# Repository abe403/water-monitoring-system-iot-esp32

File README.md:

# Water Monitoring System

An event-driven IoT telemetry pipeline from ESP32 sensor nodes through
Apache Kafka to a TimescaleDB-backed operator console, with anomaly
detection via time-series baselines and (planned) LSTM inference.

Built on top of [FerranST's open-source ESP32-C3 water-tank hardware and
firmware](https://github.com/FerranST) — see [ATTRIBUTION.md](ATTRIBUTION.md).

## Architecture

Full design, durability chain analysis, and OOD rationale:
[docs/ARCHITECTURE.md](docs/ARCHITECTURE.md)
md)

```
ESP32-C3 ──MQTT QoS1──▶ Mosquitto ──▶ ingest-gateway ──▶ Kafka ──▶ stream-processor
                                         (acks=all)        │              │
                                                           ▼              ▼
                                                    timescale-sink   inference
                                                     (idempotent)       │
                                                           │            ▼
                                                    TimescaleDB    alert-service
                                                           │            │
                                                           ▼            ▼
                                                       operations-api ──▶ console
```

## Repository layout

```
firmware/         ESPHome configs + external components (ESP32-C3 edge nodes)
hardware/         KiCad PCB design (rev-3, solar-powered)
console/          React 19 + TypeScript operator console (REST + STOMP/WebSocket)
platform/         Java 25 / Spring Boot 3.5, Gradle multi-module
  domain/           pure hexagonal core — zero framework imports (ArchUnit-enforced)
  ingest-gateway/   MQTT → Kafka durability chain (acks=all, idempotent producer)
  stream-processor/ Kafka Streams: calibration, quality flags, gap detection
  alert-service/    anomaly score consumer, alert lifecycle with hysteresis
  operations-api/   REST + WebSocket (STOMP) for the operator console
  timescale-sink/   idempotent upsert, Flyway migrations, continuous aggregates
  testing-support/  shared test fixtures
ml/               Python: feature engineering, training pipeline, anomaly detectors
simulator/        synthetic telemetry + fault injection, same 20-byte wire format
infra/            Docker Compose (Kafka KRaft, Mosquitto, TimescaleDB, Prometheus, Grafana)
tools/chaos/       3-broker conservation test with broker fault injection
docs/             architecture, ADRs, claims mapping
```

## Features

- **Firmware**: two ESPHome configs (sensing node + pump controller) validated
  against ESPHome 2026.8.1. The original fatal filter-chain bug (device never
  produced a reading due to EMA starvation under deep sleep) is fixed.
  Pump controller has dry-run protection and runtime cutoff.
- **On-device durability**: `telemetry_outbox` external component — RTC ring
  buffer surviving deep sleep, monotonic sequence numbers, application-level
  end-to-end acknowledgement (stronger than MQTT PUBACK).
- **Java platform**: full 7-module Gradle build passes. Tests cover the
  framework-free domain, MQTT→Kafka durability ordering, Kafka Streams
  enrichment and gap emission, Timescale consumer mapping, alert hysteresis,
  and Kafka→STOMP live telemetry. All adapters are wired.
- **Python ML**: 14 tests passing. Template Method training pipeline, temporal
  split with embargo, z-score/threshold/ensemble baseline detectors, full
  pipeline end-to-end on synthetic data.
- **Simulator**: 8 tests passing. Byte-identical wire encoding to the
  firmware and Java decoder.
- **Durability test**: a kind-based 3-broker Kafka harness publishes through
  MQTT and the real ingest gateway, deletes a broker during sustained load,
  and separately reports missing, unexpected, duplicate, malformed, and
  application-ack results. A recorded Podman-backed run conserved 4,000/4,000
  unique records with complete application acknowledgements while replacing
  a broker at RF=3 and `min.insync.replicas=2`; all partitions returned to
  full ISR with none unavailable or under-replicated. Its pure conservation
  oracle has 3 tests.
- **TimescaleDB schema**: 7 Flyway migrations covering hypertables, device
  registry, calibration profiles, alert table, ingest gap tracking,
  continuous aggregates (1min/1hr), and compression/retention policies.
- **Operator console**: a responsive React 19/TypeScript interface replaces
  Home Assistant for day-to-day monitoring. It provides the fleet overview,
  tank level and telemetry history, data-quality and gap diagnostics, active
  alert acknowledgement/resolution, and live STOMP updates through the same
  origin as the REST API. Seven frontend tests cover data normalization and
  the critical tank and alert surfaces.

Local verification currently covers 46 Java tests, 14 ML tests, 8 simulator
tests, 3 conservation-oracle tests, and 7 console tests: 78 tests total.

## To-Do List

The complete local pipeline has now run under Podman: a 40-record MQTT load
was conserved into Kafka with complete application acknowledgements, persisted
as 40 unique TimescaleDB rows, and exposed through the operations API. The
alert Kafka consumer and acknowledge/resolve API lifecycle were also exercised.
The replicated failure-injection run also completed successfully with 4,000
expected, observed, and unique records and no loss, duplicates, malformed
records, unexpected records, or publish errors. Real-hardware validation and
the field-data/LSTM campaign remain open.

## Prerequisites

- JDK 25 (tested with Amazon Corretto)
- Python 3.11+
- Podman plus `podman-compose` (default), or Docker Compose
- ESPHome CLI (for firmware flashing)

## Quick start

```bash
# Java platform
cd platform && ./gradlew build

# Python ML
cd ml && pip install -e ".[dev]" && pytest

# Simulator
cd simulator && pip install -e ".[dev]" && pytest

# React operator console (development server)
cd console && npm ci && npm run dev

# Full local stack (Podman default)
python -m pip install podman-compose
make up

# Docker-compatible alternative
make up CONTAINER_ENGINE=docker

# Repeat the local 40-record conservation smoke test
make conservation-local

# Three-broker failure-injection test (requires kind and kubectl)
make conservation
```

The Compose deployment serves the operator console at `http://localhost:8080`.
Nginx keeps REST (`/api/`) and STOMP/SockJS (`/ws/`) on that same origin and
proxies them to `operations-api`; no Home Assistant runtime is required.

On Windows, invoke the harness with Git Bash explicitly so `bash` does not
resolve to the Podman-machine WSL distribution:

```powershell
$env:CONTAINER_ENGINE = "podman"
$env:KIND_PROVIDER = "podman"
& "C:\Program Files\Git\bin\bash.exe" tools/chaos/run-kind.sh
```

### Windows Podman port forwarding

If Podman's Windows VirtioProxy is unhealthy, the published container ports
may appear to be listening locally while refusing connections. The portable
helper [tools/podman-port-forward.ps1](tools/podman-port-forward.ps1) uses the
Podman machine's OpenSSH endpoint and dynamically discovered container IPs,
without requiring Administrator/HNS access. It forwards the React console to
`localhost:8080`, operations API to `localhost:8084`, MQTT to
`localhost:1883`, Kafka to `localhost:9092`, and
TimescaleDB to `localhost:15432` (the host's usual PostgreSQL port, 5432, is
left untouched). When broken VirtioProxy listeners occupy those ports, the
zero-argument workflow automatically falls back to `18080` for the console,
`18084` for the API, `11883` for MQTT, and `19092` for Kafka;
`forward-status` reports the actual persisted mappings.

```powershell
# Start, verify, inspect, and stop the tunnel
make forward-start
make forward-test
make forward-status
make forward-stop
```

The helper stores only a PID and endpoint metadata under
`%LOCALAPPDATA%\water-monitoring-system-iot-esp32`; logs are stored beside it.
`Start` is idempotent and refreshes stale container IPs. It refuses to kill
unrelated processes. Pass `-StrictPorts` to demand the exact default ports
after removing a published mapping; otherwise Docker remains supported by the
normal Compose targets and this helper is a Windows Podman fallback.

## Decisions

Architectural decisions are recorded in `docs/DECISIONS/`:

- [0000](docs/DECISIONS/0000-security-remediation.md) — Security remediation
- [0001](docs/DECISIONS/0001-mqtt-over-native-api.md) — MQTT over HA native API
- [0002](docs/DECISIONS/0002-server-side-calibration.md) — Server-side calibration
- [0003](docs/DECISIONS/0003-keep-arduino-framework.md) — Keep Arduino framework
- [0004](docs/DECISIONS/0004-server-side-liveness.md) — Server-side liveness
- [0005](docs/DECISIONS/0005-pod-structs-in-rtc-memory.md) — POD structs in RTC memory
- [0006](docs/DECISIONS/0006-dry-run-protection.md) — Dry-run protection fails closed

## License

See [LICENSE](LICENSE).

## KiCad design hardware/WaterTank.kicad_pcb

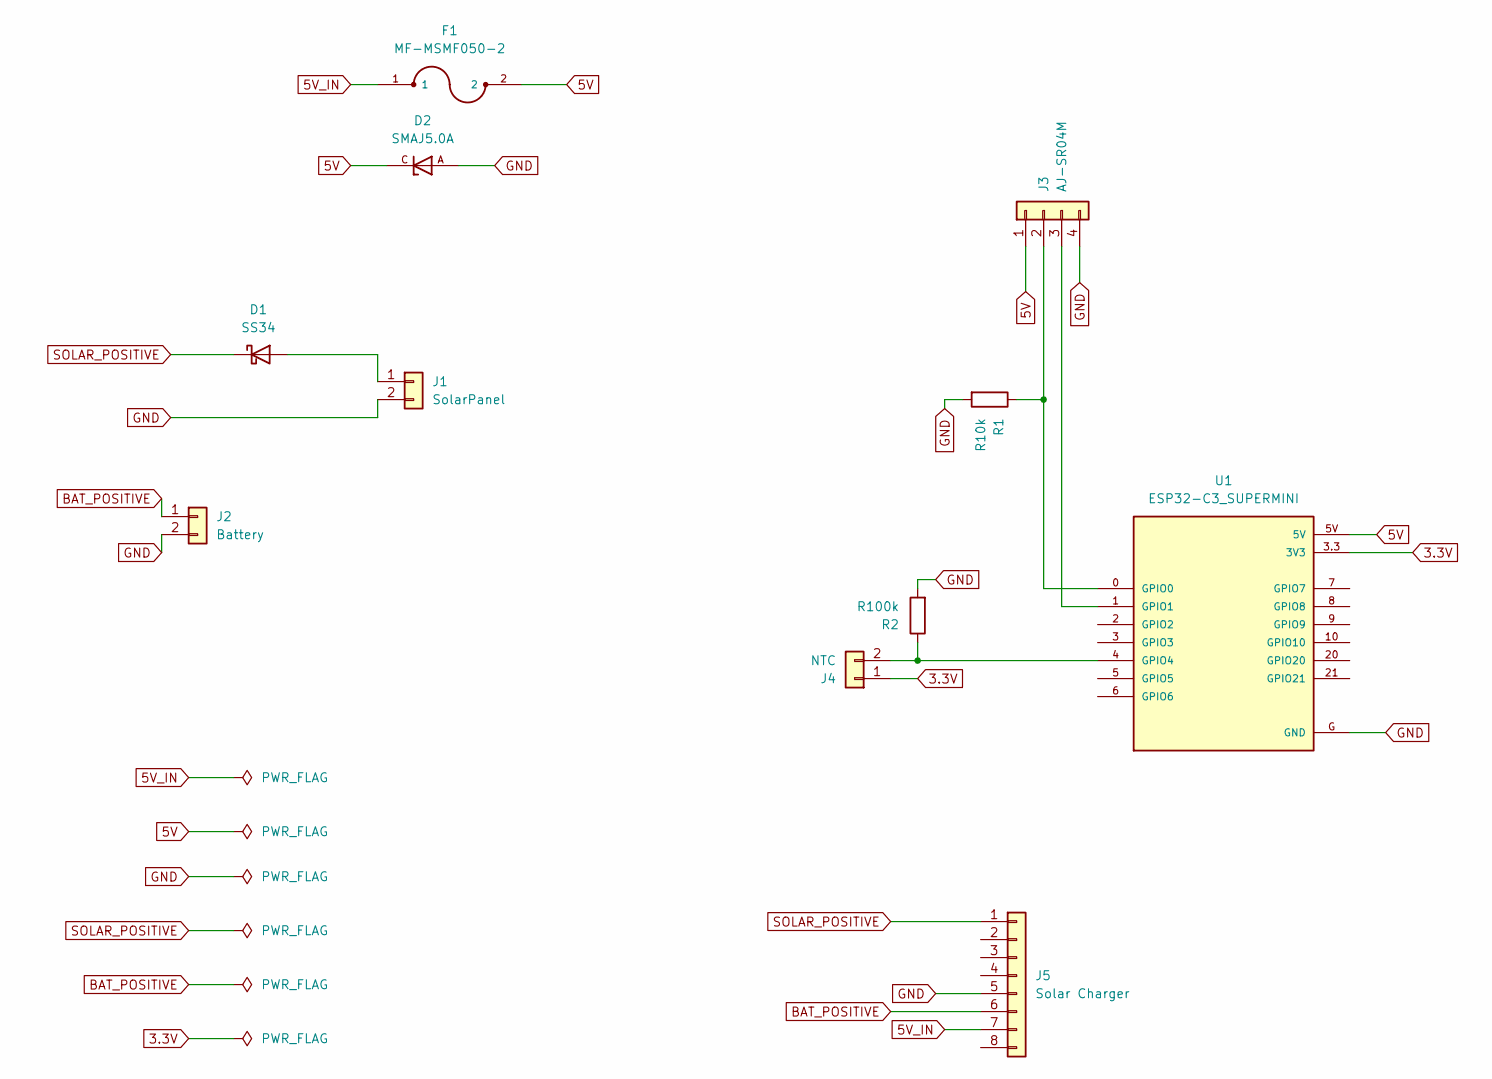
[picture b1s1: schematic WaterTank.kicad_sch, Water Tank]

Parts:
D1: SS34; D_SMA_Handsoldering
D2: SMAJ5.0A; DIOM4325X250N; PARTREV S2102
F1: MF-MSMF050-2; FUSM4632X85; DigiKey_Part_Number MF-MSMF050-2TR-ND
J1: SolarPanel; JST_XH_B2B-XH-A_1x02_P2.50mm_Vertical
J2: Battery; JST_XH_B2B-XH-A_1x02_P2.50mm_Vertical
J3: AJ-SR04M; PinHeader_1x04_P2.54mm_Vertical
J4: NTC; JST_XH_B2B-XH-A_1x02_P2.50mm_Vertical
J5: Solar Charger; PinHeader_1x08_P2.54mm_Vertical
R1: R10k; R_0805_2012Metric_Pad1.20x1.40mm_HandSolder
R2: R100k; R_0805_2012Metric_Pad1.20x1.40mm_HandSolder
U1: ESP32-C3_SUPERMINI; MODULE_ESP32-C3_SUPERMINI_SMD

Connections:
3.3V: J4.1, U1.3.3 (3V3)
5V: D2.C, F1.2, J3.1, U1.5V
5V_IN: F1.1, J5.7
BAT_POSITIVE: J2.1, J5.6
GND: D2.A, J1.2, J2.2, J3.4, J5.5, R1.2, R2.2, U1.G (GND)
unnamed: D1.2 (A), J1.1
unnamed: J3.2, R1.1, U1.0 (GPIO0)
unnamed: J3.3, U1.1 (GPIO1)
unnamed: J4.2, R2.1, U1.4 (GPIO4)
SOLAR_POSITIVE: D1.1 (K), J5.1

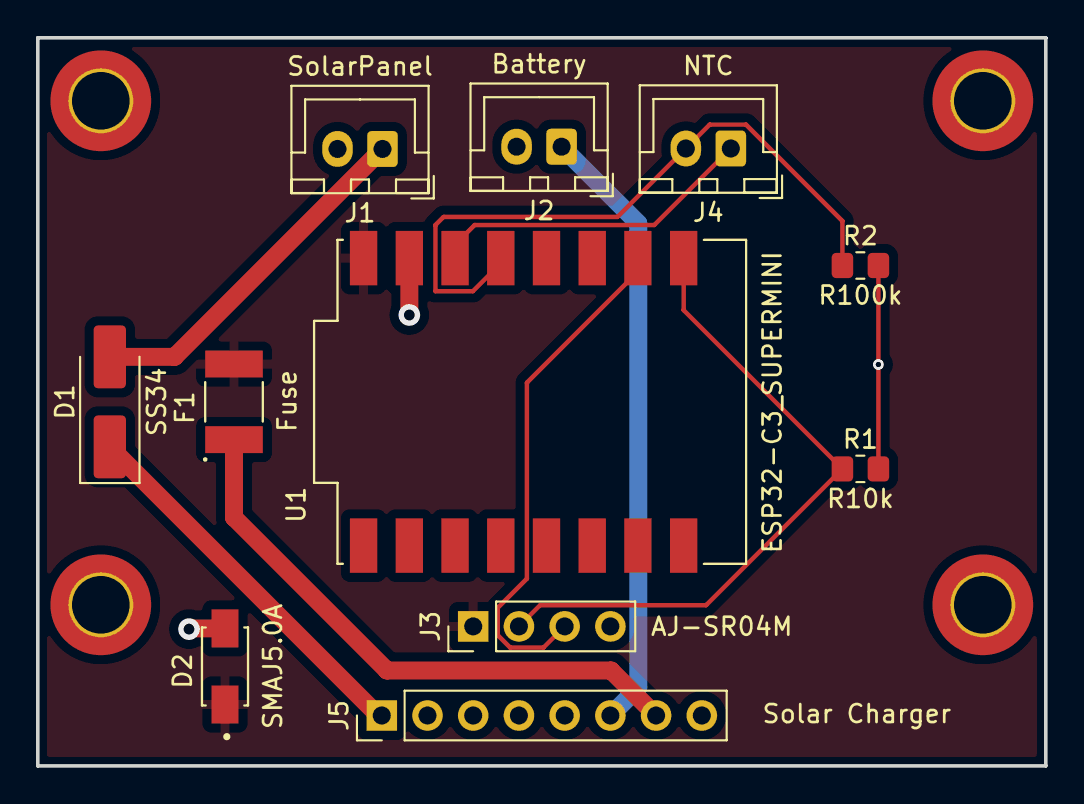
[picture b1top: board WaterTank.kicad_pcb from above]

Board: 2 copper layers, 56.0 x 40.5 mm, 11 parts (0 on the bottom side), 10 nets.

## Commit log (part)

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2026-04-28 docs: add comprehensive emoji-free readme for water monitoring system
2026-04-29 chore: add .gitignore to protect secrets
2026-04-29 forced commit to unstuck
2026-05-17 feat: added Power BI telemetry integration and upgraded E2E Selenium validation framework
